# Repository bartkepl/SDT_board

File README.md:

# SDT (SCPI Display Thermometer)
Benchtop thermometer with SCPI and USB.

---
## Status : WIP

- [x] First revision of schematic and PCB is done.
- [x] PCB and parts ordered
- [x] Prototypes assembled and tested 
- [x] Firmware (v3.1)

---
## Features:
- 4 layer board
- ARM Cortex-M0+ Processor in LQFP48 (STM32C071CBT6) 
- USB 2.0
- TMP117 or/and SHT45 for temperature measurement
----

## License and Contribution

Idea based on [SCPI Capable Thermometer](https://sebastianharnisch.de/scpi-enabled-thermometer/)

Display part & footprint from [kicad-intelligent-displays](https://github.com/74hc595/kicad-intelligent-displays) by [74hc595](https://github.com/74hc595)

USB-TMC library from TinyUSB [TinyUSB](https://github.com/hathach/tinyusb)

SCPI parser library from [scpi-parser](https://github.com/j123b567/scpi-parser) by [Jan Breuer](https://github.com/j123b567)

[MIT License](/LICENSE)

Open to contributions in both software and hardware!

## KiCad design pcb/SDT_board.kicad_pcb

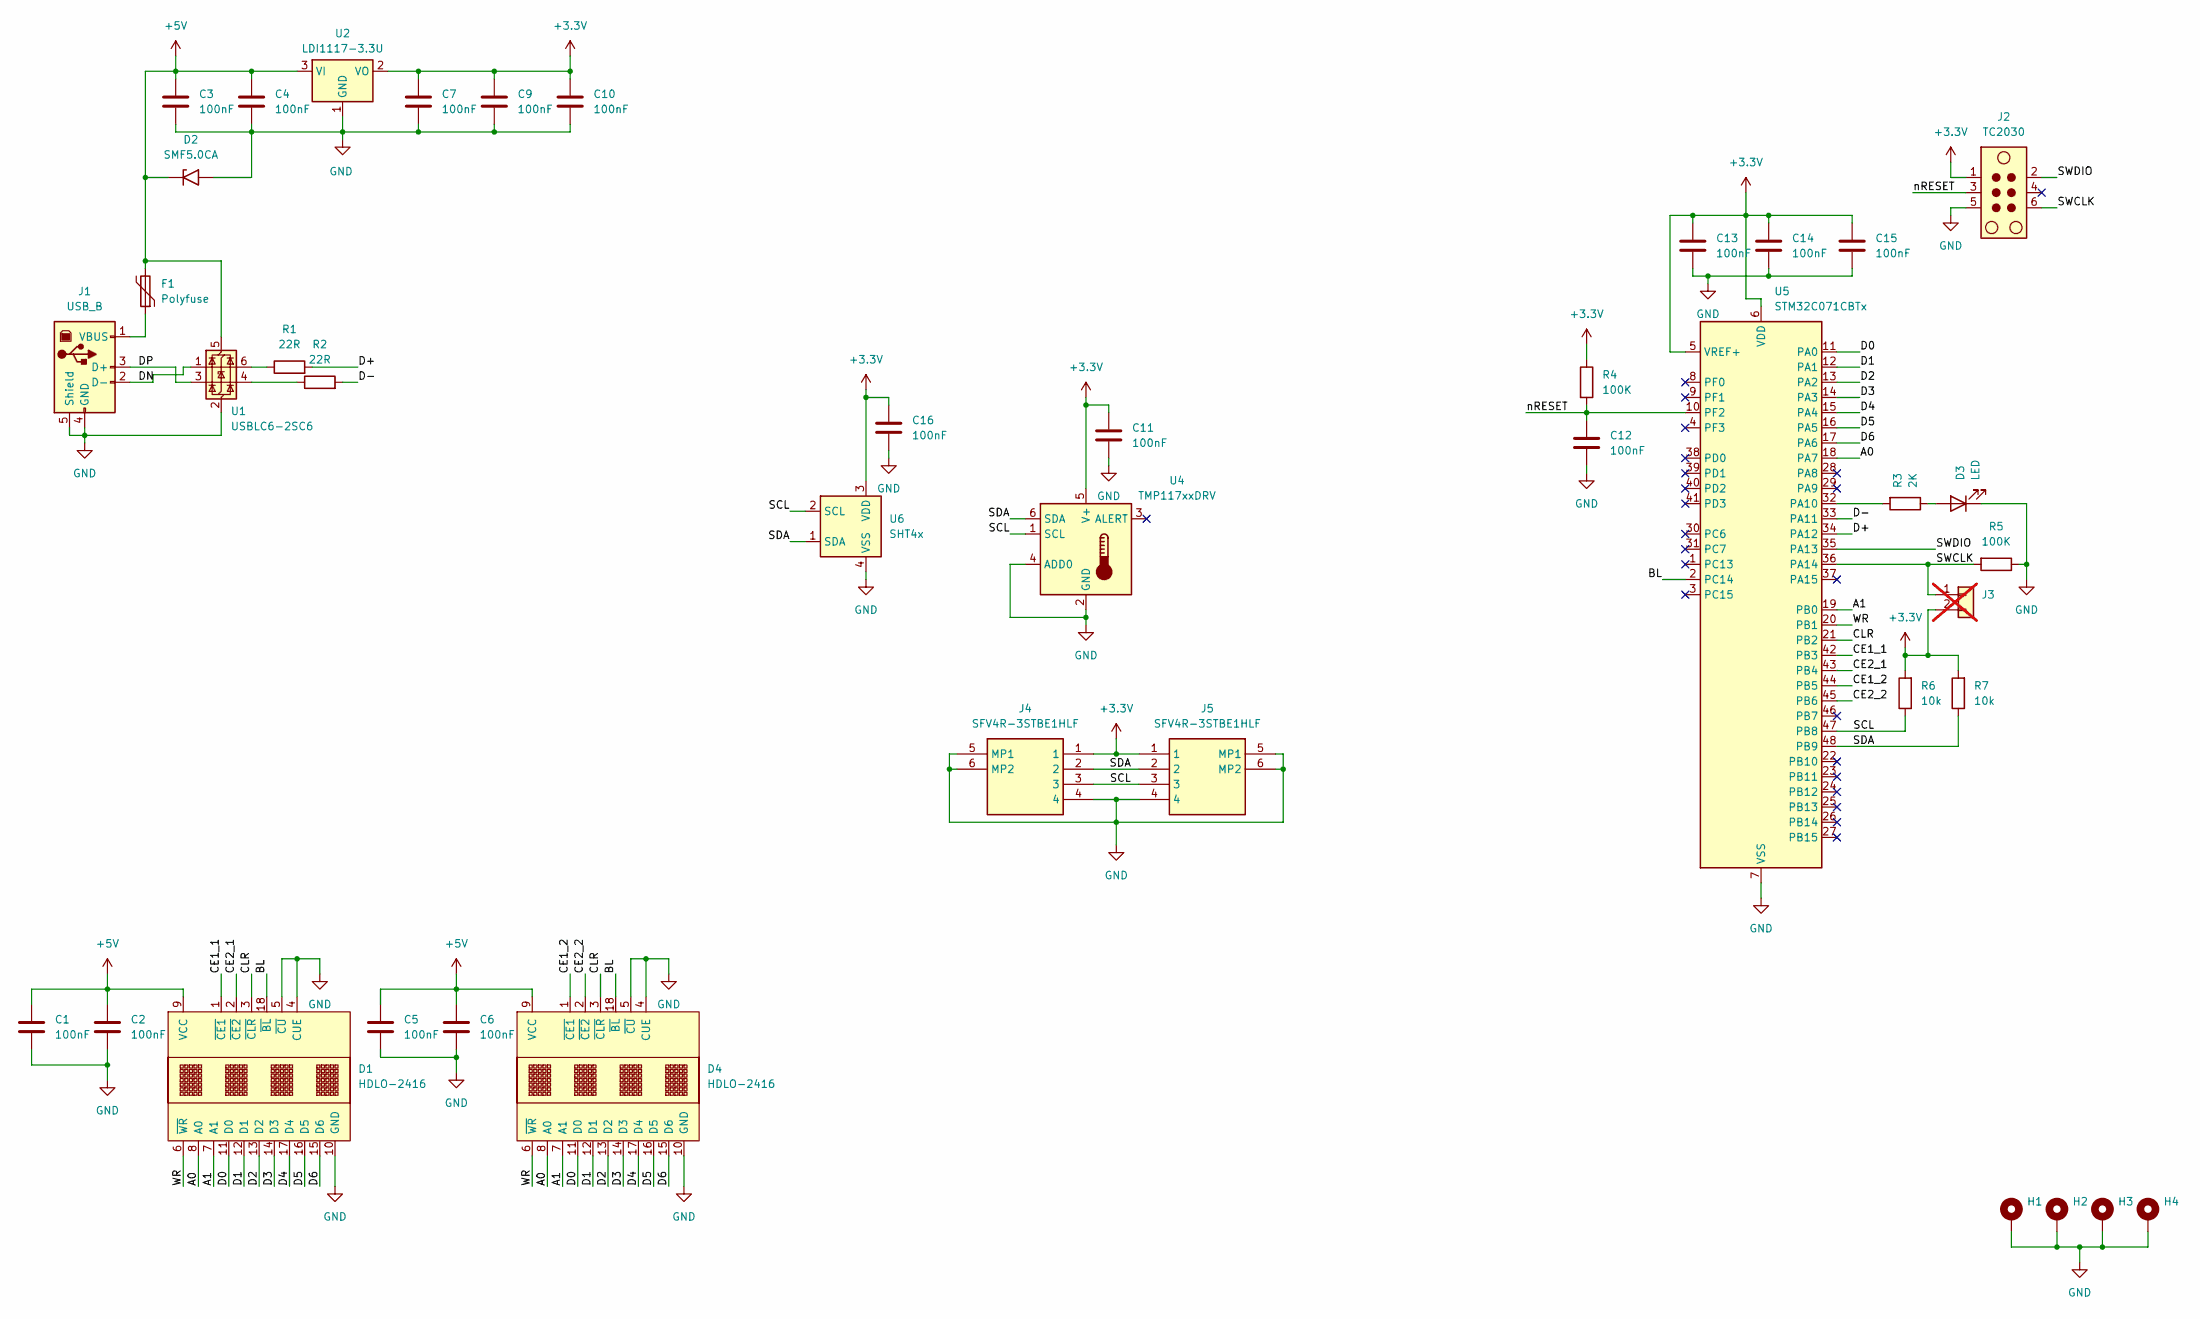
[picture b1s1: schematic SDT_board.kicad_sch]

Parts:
C1, C2, C3, C4, C5, C6, C7, C9, C10, C11, C12, C13, C14, C15, C16: 100nF; C_0603_1608Metric_Pad1.08x0.95mm_HandSolder
D1, D4: HDLO-2416; DL2416
D2: SMF5.0CA; D_SMF
D3: LED; LED_0603_1608Metric_Pad1.05x0.95mm_HandSolder
F1: Polyfuse; Fuse_1206_3216Metric_Pad1.42x1.75mm_HandSolder
H1, H2, H3, H4: MountingHole_Pad; MountingHole_3.2mm_M3_Pad
J1: USB_B; JST_PH_B4B-PH-K_1x04_P2.00mm_Vertical
J2: TC2030; Tag-Connect_TC2030-IDC-NL_2x03_P1.27mm_Vertical
J3: Conn_01x02; PinHeader_1x02_P2.54mm_Vertical; not fitted
J4, J5: SFV4R-3STBE1HLF; SFV4R3STBE1HLF; Manufacturer_Part_Number SFV4R-3STBE1HLF
R1, R2: 22R; R_0603_1608Metric_Pad0.98x0.95mm_HandSolder
R3: 2K; R_0603_1608Metric_Pad0.98x0.95mm_HandSolder
R4, R5: 100K; R_0603_1608Metric_Pad0.98x0.95mm_HandSolder
R6, R7: 10k; R_0603_1608Metric_Pad0.98x0.95mm_HandSolder
U1: USBLC6-2SC6; SOT-23-6_Handsoldering
U2: LDI1117-3.3U; SOT-89-3_Handsoldering
U4: TMP117xxDRV; WSON-6-1EP_2x2mm_P0.65mm_EP1x1.6mm
U5: STM32C071CBTx; LQFP-48_7x7mm_P0.5mm
U6: SHT4x; Sensirion_DFN-4_1.5x1.5mm_P0.8mm_SHT4x_NoCentralPad

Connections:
+3.3V: C7.1, C9.1, C10.1, C11.1, C13.1, C14.1, C15.1, C16.1, J2.1, J3.2, J4.1, J5.1, R4.1, R6.2, R7.2, U2.2 (VO), U4.5 (V+), U5.5 (VREF+), U5.6 (VDD), U6.3 (VDD)
+5V: C1.1, C2.1, C3.1, C4.1, C5.1, C6.1, D1.9 (VCC), D2.1 (A1), D4.9 (VCC), F1.2, U1.5 (VBUS), U2.3 (VI)
/A0: D1.8 (A0), D4.8 (A0), U5.18 (PA7)
/A1: D1.7 (A1), D4.7 (A1), U5.19 (PB0)
/BL: D1.18 (~BL), D4.18 (~BL), U5.2 (PC14)
/CE1_1: D1.1 (~CE1), U5.42 (PB3)
/CE1_2: D4.1 (~CE1), U5.44 (PB5)
/CE2_1: D1.2 (~CE2), U5.43 (PB4)
/CE2_2: D4.2 (~CE2), U5.45 (PB6)
/CLR: D1.3 (~CLR), D4.3 (~CLR), U5.21 (PB2)
/D0: D1.11 (D0), D4.11 (D0), U5.11 (PA0)
/D1: D1.12 (D1), D4.12 (D1), U5.12 (PA1)
/D2: D1.13 (D2), D4.13 (D2), U5.13 (PA2)
/D3: D1.14 (D3), D4.14 (D3), U5.14 (PA3)
/D4: D1.17 (D4), D4.17 (D4), U5.15 (PA4)
/D5: D1.16 (D5), D4.16 (D5), U5.16 (PA5)
/D6: D1.15 (D6), D4.15 (D6), U5.17 (PA6)
/D+: R1.2, U5.34 (PA12)
/D-: R2.2, U5.33 (PA11)
/DN: J1.2 (D-), U1.1 (I/O1)
/DP: J1.3 (D+), U1.3 (I/O2)
/SCL: J4.3, J5.3, R6.1, U4.1 (SCL), U5.47 (PB8), U6.2 (SCL)
/SDA: J4.2, J5.2, R7.1, U4.6 (SDA), U5.48 (PB9), U6.1 (SDA)
/SWCLK: J2.6, J3.1, R5.2, U5.36 (PA14)
/SWDIO: J2.2, U5.35 (PA13)
/WR: D1.6 (~WR), D4.6 (~WR), U5.20 (PB1)
/nRESET: C12.1, J2.3, R4.2, U5.10 (PF2)
GND: C1.2, C2.2, C3.2, C4.2, C5.2, C6.2, C7.2, C9.2, C10.2, C11.2, C12.2, C13.2, C14.2, C15.2, C16.2, D1.4 (CUE), D1.5 (~CU), D1.10 (GND), D2.2 (A2), D3.1 (K), D4.4 (CUE), D4.5 (~CU), D4.10 (GND), H1.1, H2.1, H3.1, H4.1, J1.4 (GND), J1.5 (Shield), J2.5, J4.4, J4.5 (MP1), J4.6 (MP2), J5.4, J5.5 (MP1), J5.6 (MP2), R5.1, U1.2 (GND), U2.1 (GND), U4.2 (GND), U4.4 (ADD0), U5.7 (VSS), U6.4 (VSS)
unnamed: D3.2 (A), R3.1
unnamed: F1.1, J1.1 (VBUS)
unnamed: R1.1, U1.6 (I/O1)
unnamed: R2.1, U1.4 (I/O2)
unnamed: R3.2, U5.32 (PA10)

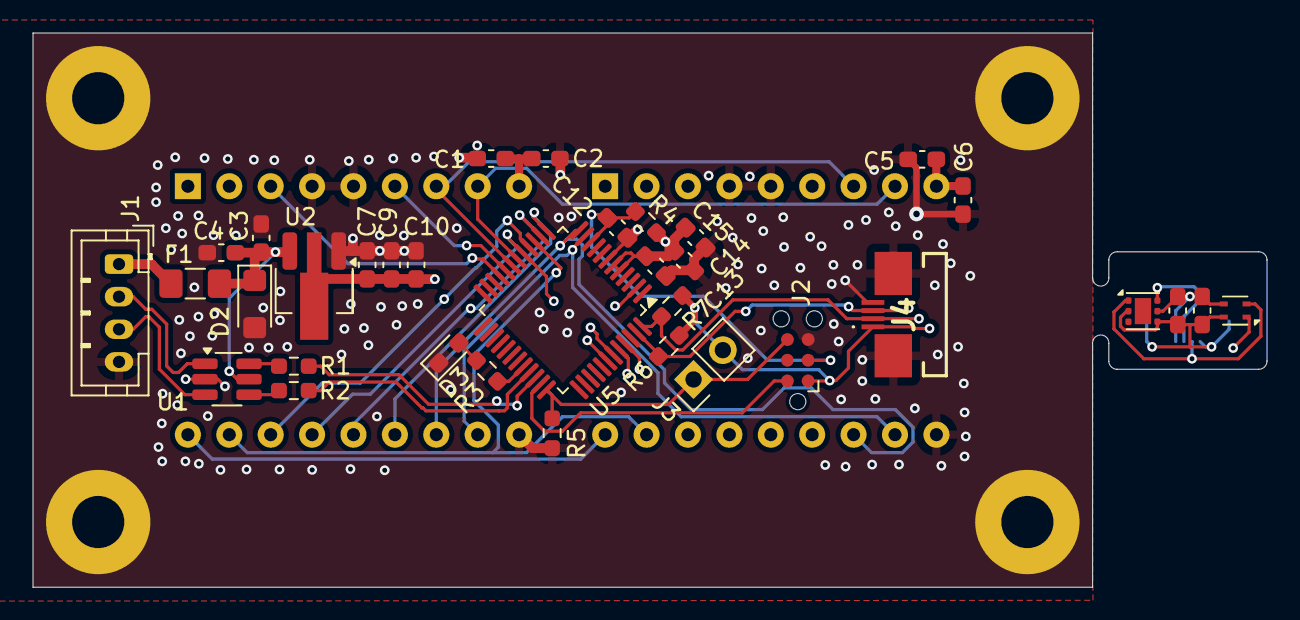
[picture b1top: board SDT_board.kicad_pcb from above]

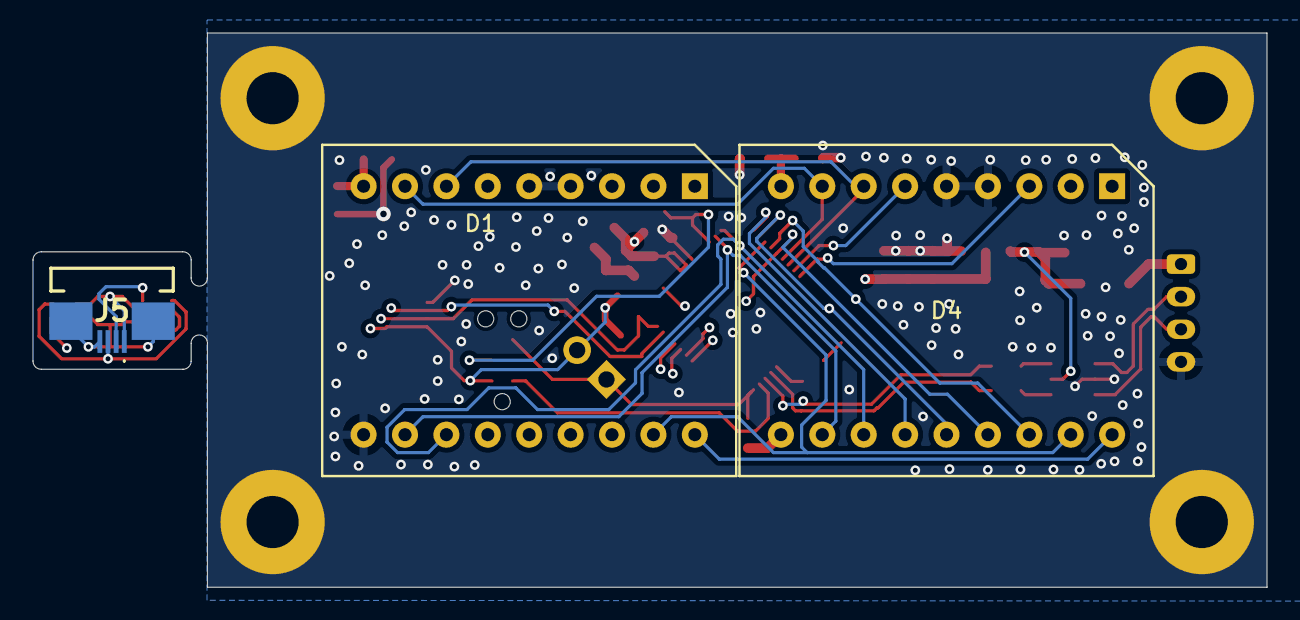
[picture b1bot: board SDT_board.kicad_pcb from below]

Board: 4 copper layers, 75.7 x 34.0 mm, 41 parts (3 on the bottom side), 33 nets.

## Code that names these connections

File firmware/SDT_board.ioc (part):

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Mcu.Name=STM32C071CBTx
Mcu.Package=LQFP48_GP
Mcu.UserName=STM32C071CBTx
PA0.GPIOParameters=GPIO_Label
PA0.GPIO_Label=D0
PA0.Signal=GPIO_Output
PA1.GPIOParameters=GPIO_Label
PA1.GPIO_Label=D1
PA1.Signal=GPIO_Output
PA10.GPIOParameters=GPIO_Label
PA10.GPIO_Label=LED
PA10.Signal=GPIO_Output
PA11\ [PA9].Mode=Device
PA11\ [PA9].Signal=USB_DM
PA12\ [PA10].Mode=Device
PA12\ [PA10].Signal=USB_DP
PA13.Mode=Serial_Wire
PA13.Signal=DEBUG_SWDIO
PA14-BOOT0.Mode=Serial_Wire
PA14-BOOT0.Signal=DEBUG_SWCLK
PA2.GPIOParameters=GPIO_Label
PA2.GPIO_Label=D2
PA2.Signal=GPIO_Output
PA3.GPIOParameters=GPIO_Label
PA3.GPIO_Label=D3
PA3.Signal=GPIO_Output
PA4.GPIOParameters=GPIO_Label
PA4.GPIO_Label=D4
PA4.Signal=GPIO_Output
PA5.GPIOParameters=GPIO_Label
PA5.GPIO_Label=D5
PA5.Signal=GPIO_Output
PA6.GPIOParameters=GPIO_Label
PA6.GPIO_Label=D6
PA6.Signal=GPIO_Output
PA7.GPIOParameters=GPIO_Label
PA7.GPIO_Label=A0
PA7.Signal=GPIO_Output
PB0.GPIOParameters=GPIO_Label
PB0.GPIO_Label=A1
PB0.Signal=GPIO_Output
PB1.GPIOParameters=GPIO_Label
PB1.GPIO_Label=WR
PB1.Signal=GPIO_Output
PB2.GPIOParameters=GPIO_Label
PB2.GPIO_Label=CLR
PB2.Signal=GPIO_Output
PB3.GPIOParameters=GPIO_Label
PB3.GPIO_Label=CE1_1
PB3.Signal=GPIO_Output
PB4.GPIOParameters=GPIO_Label
PB4.GPIO_Label=CE2_1
PB4.Signal=GPIO_Output
PB5.GPIOParameters=GPIO_Label
PB5.GPIO_Label=CE1_2
PB5.Signal=GPIO_Output
PB6.GPIOParameters=GPIO_Label
PB6.GPIO_Label=CE2_2
PB6.Signal=GPIO_Output
PB8.Mode=I2C
PB8.Signal=I2C1_SCL
PB9.Mode=I2C
PB9.Signal=I2C1_SDA
PC14-OSCX_IN(PC14).GPIOParameters=GPIO_Label
PC14-OSCX_IN(PC14).GPIO_Label=BL
PC14-OSCX_IN(PC14).Signal=S_TIM3_CH2
RCC.HSE_VALUE=8000000
RCC.SYSCLKFreq_VALUE=12000000
RCC.SYSCLKSource=RCC_SYSCLKSOURCE_HSIUSB48
board=custom

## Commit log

2026-03-16 Test firmware
2026-03-18 New test firmware
2026-03-19 New USB-TMC firmware, updated Readme
2026-03-19 All modules working, needs refining
2026-03-20 More firmware updates/features. Added python companion gui app
2026-03-23 More updates and fixes
2026-03-24 New display task,scpi fixes and modifications
2026-03-26 Added Serial No based on DevId Hash, started rewriting Sensor to State machine
2026-05-05 Testing new sensor state machine
2026-05-05 More dev
2026-05-06 State machine working
2026-05-06 Added new functionality, deleted USB-CDC as discontinued
2026-05-07 Working new functionality (period, avg, prec)
2026-05-07 Cleaning done by claude code
2026-05-07 Better TMP117 by Claude Code
2026-05-07 Updated functionallity by claude code
2026-05-08 SCPI error handling by claude
2026-05-08 Added documentation created by claude
2026-05-08 Cleaning
2026-05-08 New companion app by claude
2026-05-11 SDT App in .NET8 + WPF by Claude
2026-05-13 Repo cleaning and few fixes
2026-05-18 Implement persistent configuration storage with DEFAULT, PRIMARY, and BACKUP tiers
    - Updated flash.c and flash.h to support a 3-tier configuration storage system.
    - Introduced functions for saving, restoring, and recalling configurations.
    - Added CRC validation for configuration integrity.
    - Integrated configuration management into SCPI command set.
    - Adjusted memory layout in linker script for new configuration storage.
    - Updated firmware version in scpi-def.h to 3.2.
2026-05-18 Update TODO list and enhance error handling in SCPI commands
    - Mark completed tasks in the TODO list.
    - Improve error handling for communication errors in SCPI commands.
    - Add checks for device connection status during polling.
    - Clean up commented-out code in USB-TMC application.
2026-05-18 Add polynomial calibration functionality and SCPI commands for calibration management
2026-05-19 Add polynomial calibration support with degree up to 5 and update SCPI commands
2026-05-19 Add localization support for English and Polish, enhance error handling in sensor communication
2026-05-20 Lang fix
